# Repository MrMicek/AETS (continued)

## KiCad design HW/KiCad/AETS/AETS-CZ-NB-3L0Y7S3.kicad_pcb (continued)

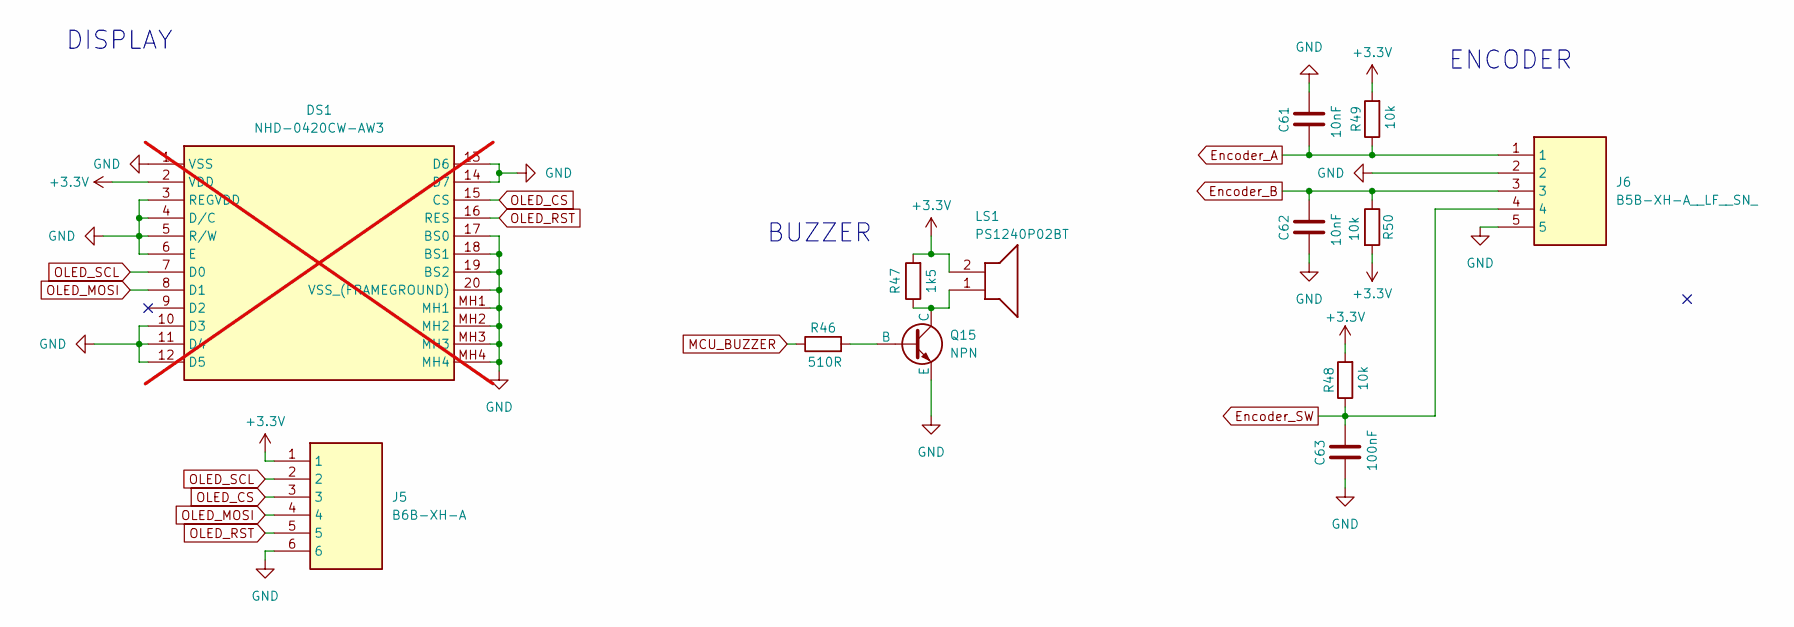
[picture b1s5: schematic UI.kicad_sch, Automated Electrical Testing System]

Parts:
C61, C62: 10nF; C_0805_2012Metric
C63: 100nF; C_0805_2012Metric
DS1: NHD-0420CW-AW3; NHD0420CWAW3; Manufacturer_Part_Number NHD-0420CW-AW3; not fitted
J5: B6B-XH-A; B6BXHA; Manufacturer_Part_Number B6B-XH-A
J6: B5B-XH-A__LF__SN_; SHDR5W64P0X250_1X5_1490X575X700P; Manufacturer_Part_Number B5B-XH-A (LF)(SN)
LS1: PS1240P02BT; Mouser Part Number 810-PS1240P02BT
Q15: NPN; SOT95P240X120-3N
R46: 510R; R_0805_2012Metric
R47: 1k5; R_0603_1608Metric
R48, R49, R50: 10k; R_0805_2012Metric

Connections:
+3.3V: DS1.2 (VDD), J5.1, LS1.2, R47.2, R48.2, R49.2, R50.2; also elsewhere on the board
Encoder_A: C61.2, J6.1, R49.1; also elsewhere on the board
Encoder_B: C62.1, J6.3, R50.1; also elsewhere on the board
Encoder_SW: C63.1, J6.4, R48.1; also elsewhere on the board
GND: C61.1, C62.2, C63.2, DS1.1 (VSS), DS1.3 (REGVDD), DS1.4 (D/C), DS1.5 (R/W), DS1.6 (E), DS1.10 (D3), DS1.11 (D4), DS1.12 (D5), DS1.13 (D6), DS1.14 (D7), DS1.17 (BS0), DS1.18 (BS1), DS1.19 (BS2), DS1.20 (VSS_(FRAMEGROUND)), DS1.MH1, DS1.MH2, DS1.MH3, DS1.MH4, J5.6, J6.2, J6.5, Q15.2 (E); also elsewhere on the board
MCU_BUZZER: R46.1; also elsewhere on the board
unnamed: Q15.1 (B), R46.2
unnamed: LS1.1, Q15.3 (C), R47.1
OLED_CS: DS1.15 (CS), J5.3; also elsewhere on the board
OLED_MOSI: DS1.8 (D1), J5.4; also elsewhere on the board
OLED_RST: DS1.16 (RES), J5.5; also elsewhere on the board
OLED_SCL: DS1.7 (D0), J5.2; also elsewhere on the board

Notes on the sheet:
BUZZER
DISPLAY
ENCODER

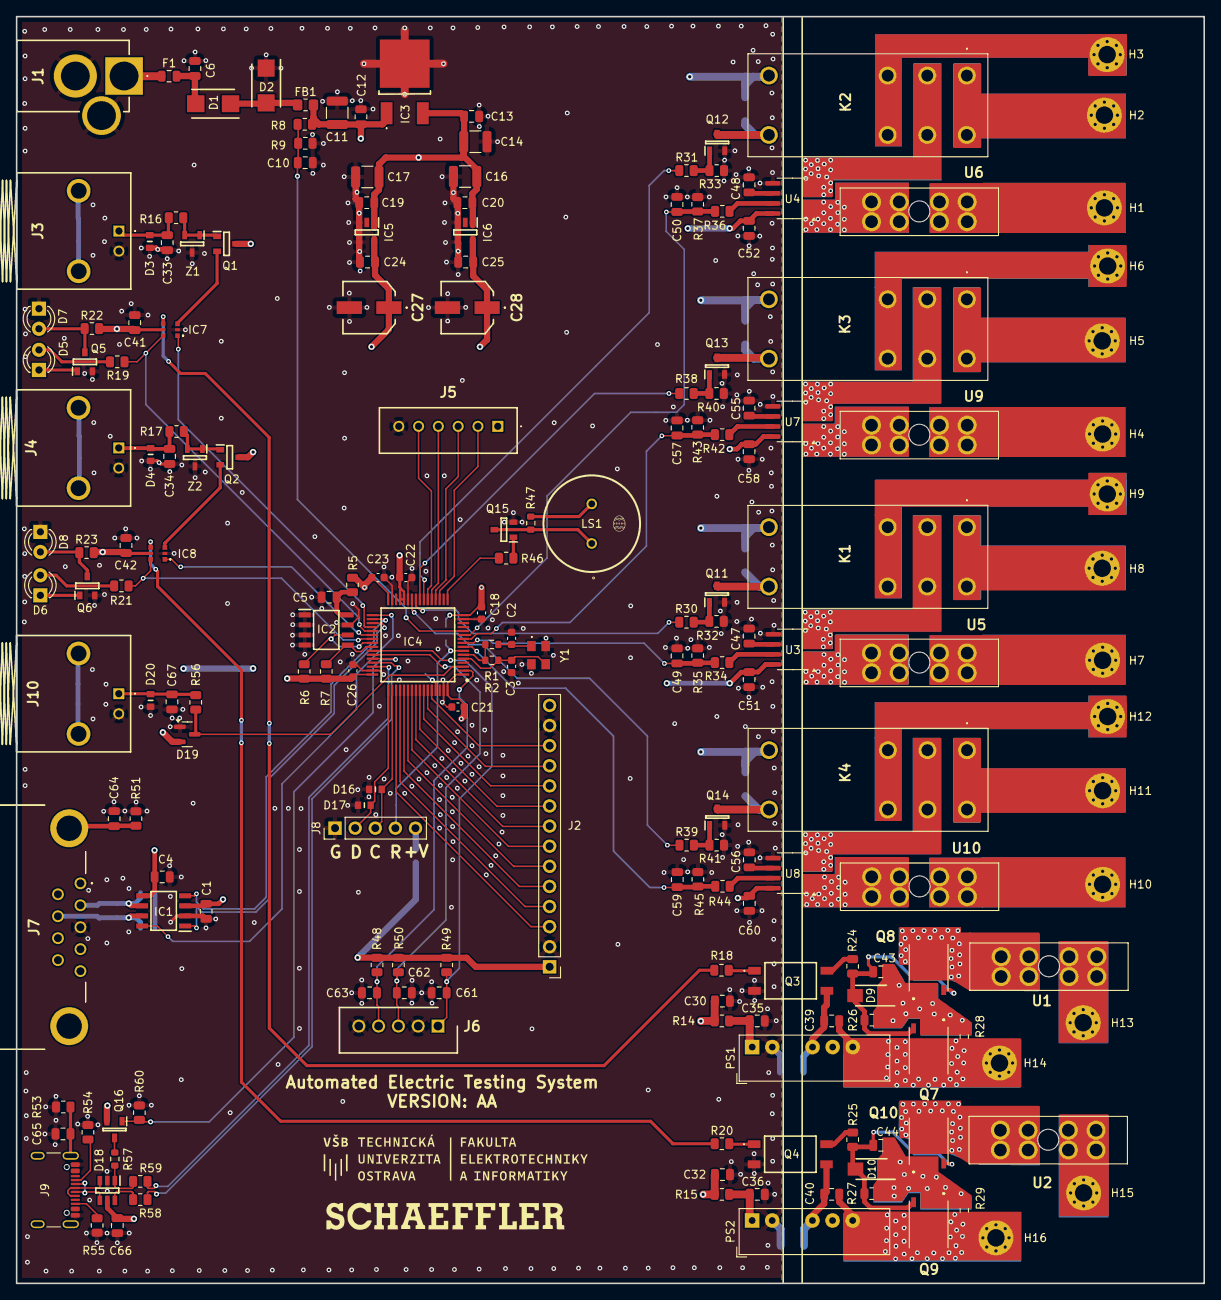
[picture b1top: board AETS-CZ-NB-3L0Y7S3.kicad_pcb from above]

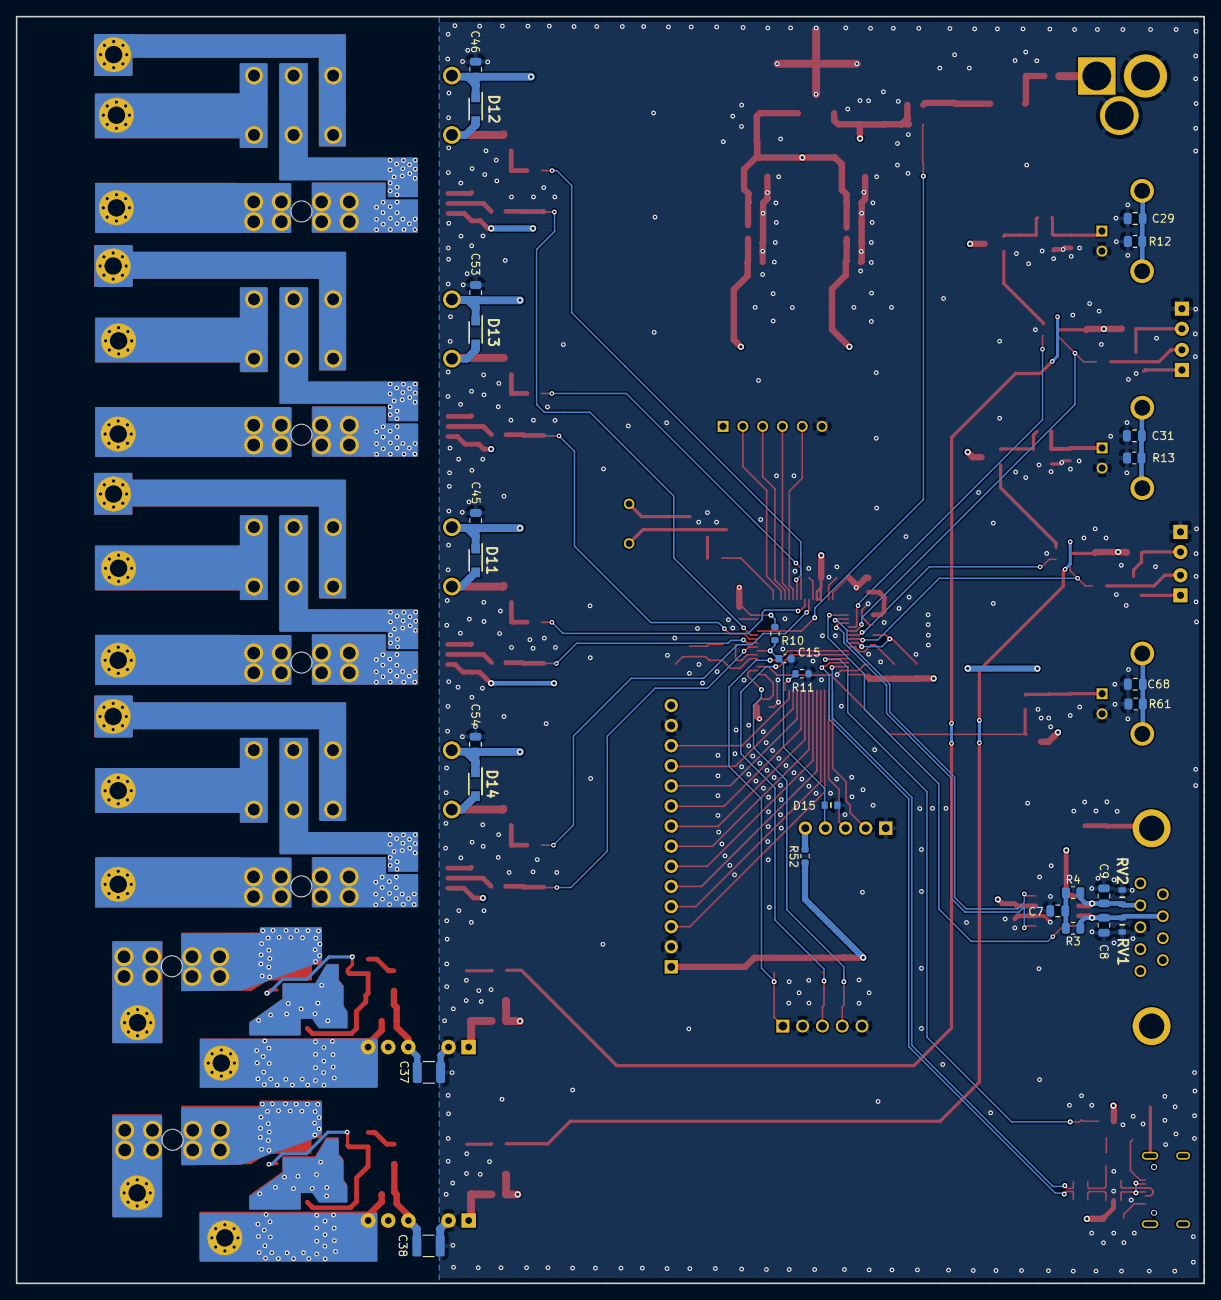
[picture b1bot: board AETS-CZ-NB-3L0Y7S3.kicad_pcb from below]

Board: 4 copper layers, 150.0 x 160.0 mm, 223 parts (28 on the bottom side), 143 nets.

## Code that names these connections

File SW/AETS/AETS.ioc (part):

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Mcu.Name=STM32G474R(B-C-E)Tx
Mcu.Package=LQFP64
Mcu.UserName=STM32G474RETx
PA0.GPIOParameters=GPIO_Label
PA0.GPIO_Label=ADC_VBUS
PA0.Mode=IN1-Single-Ended
PA0.Signal=ADC2_IN1
PA1.GPIOParameters=GPIO_Label
PA1.GPIO_Label=NOTUSED
PA1.Signal=GPIO_Output
PA10.GPIOParameters=GPIO_Label
PA10.GPIO_Label=USB_DIS
PA10.Signal=GPIO_Output
PA11.Mode=Device
PA11.Signal=USB_DM
PA12.Mode=Device
PA12.Signal=USB_DP
PA13.Mode=Serial_Wire
PA13.Signal=SYS_JTMS-SWDIO
PA14.Mode=Serial_Wire
PA14.Signal=SYS_JTCK-SWCLK
PA15.GPIOParameters=GPIO_Label
PA15.GPIO_Label=NOTUSED
PA15.Signal=GPIO_Output
PA2.GPIOParameters=GPIO_Label
PA2.GPIO_Label=NOTUSED
PA2.Signal=GPIO_Output
PA3.GPIOParameters=GPIO_Speed,GPIO_Label
PA3.GPIO_Label=BUZZER
PA3.GPIO_Speed=GPIO_SPEED_FREQ_HIGH
PA3.Signal=S_TIM5_CH4
PA4.GPIOParameters=GPIO_Label
PA4.GPIO_Label=NOTUSED
PA4.Signal=GPIO_Output
PA5.GPIOParameters=GPIO_Label
PA5.GPIO_Label=OLED_SCK
PA5.Mode=Simplex_Bidirectional_Master
PA5.Signal=SPI1_SCK
PA6.GPIOParameters=GPIO_Label
PA6.GPIO_Label=OLED_CS
PA6.Signal=GPIO_Output
PA7.GPIOParameters=GPIO_Label
PA7.GPIO_Label=OLED_MOSI
PA7.Mode=Simplex_Bidirectional_Master
PA7.Signal=SPI1_MOSI
PA8.GPIOParameters=GPIO_Speed,GPIO_Label
PA8.GPIO_Label=ENCODER_A
PA8.GPIO_Speed=GPIO_SPEED_FREQ_MEDIUM
PA8.Signal=S_TIM1_CH1
PA9.GPIOParameters=GPIO_Speed,GPIO_Label
PA9.GPIO_Label=ENCODER_B
PA9.GPIO_Speed=GPIO_SPEED_FREQ_MEDIUM
PA9.Signal=S_TIM1_CH2
PB0.GPIOParameters=GPIO_Label
PB0.GPIO_Label=GPIO_RELAY2
PB0.Signal=GPIO_Output
PB1.GPIOParameters=GPIO_Label
PB1.GPIO_Label=GPIO_RELAY3
PB1.Signal=GPIO_Output
PB10.GPIOParameters=GPIO_Label
PB10.GPIO_Label=NOTUSED
PB10.Signal=GPIO_Output
PB11.GPIOParameters=GPIO_Label
PB11.GPIO_Label=CAN_STB
PB11.Signal=GPIO_Output
PB12.GPIOParameters=GPIO_Speed,GPIO_Label
PB12.GPIO_Label=CAN_RXD
PB12.GPIO_Speed=GPIO_SPEED_FREQ_HIGH
PB12.Mode=FDCAN_Activate
PB12.Signal=FDCAN2_RX
PB13.GPIOParameters=GPIO_Speed,GPIO_Label
PB13.GPIO_Label=CAN_TXD
PB13.GPIO_Speed=GPIO_SPEED_FREQ_HIGH
PB13.Mode=FDCAN_Activate
PB13.Signal=FDCAN2_TX
PB14.GPIOParameters=GPIO_Label
PB14.GPIO_Label=GPIO_MOSFET1
PB14.Signal=GPIO_Output
PB15.GPIOParameters=GPIO_Label
PB15.GPIO_Label=GPIO_MUX1
PB15.Signal=GPIO_Output
PB2.GPIOParameters=GPIO_Label
PB2.GPIO_Label=GPIO_RELAY4
PB2.Signal=GPIO_Output
PB3.GPIOParameters=GPIO_Label
PB3.GPIO_Label=NOTUSED
PB3.Signal=GPIO_Output
PB4.GPIOParameters=GPIO_Label
PB4.GPIO_Label=NOTUSED
PB4.Signal=GPIO_Output
PB5.GPIOParameters=GPIO_Label
PB5.GPIO_Label=NOTUSED
PB5.Signal=GPIO_Output
PB6.GPIOParameters=GPIO_Label
PB6.GPIO_Label=NOTUSED
PB6.Signal=GPIO_Output
PB7.GPIOParameters=GPIO_Label
PB7.GPIO_Label=NOTUSED
PB7.Signal=GPIO_Output
PB9.GPIOParameters=GPIO_Label
PB9.GPIO_Label=NOTUSED
PB9.Signal=GPIO_Output
PC0.GPIOParameters=GPIO_Label,GPIO_Pd
PC0.GPIO_Label=ADC_RELAY4
PC0.GPIO_Pd=GPIO_NOPULL
PC0.Mode=IN6-Single-Ended
PC0.Signal=ADC1_IN6
PC1.GPIOParameters=GPIO_Label,GPIO_Pd
PC1.GPIO_Label=ADC_RELAY3
PC1.GPIO_Pd=GPIO_NOPULL
PC1.Mode=IN7-Single-Ended
PC1.Signal=ADC1_IN7
PC10.GPIOParameters=GPIO_Label
PC10.GPIO_Label=NOTUSED
PC10.Signal=GPIO_Output
PC11.GPIOParameters=GPIO_Label
PC11.GPIO_Label=NOTUSED
PC11.Signal=GPIO_Output
PC12.GPIOParameters=GPIO_Label
PC12.GPIO_Label=NOTUSED
PC12.Signal=GPIO_Output
PC13.GPIOParameters=GPIO_Label,GPIO_ModeDefaultEXTI
PC13.GPIO_Label=ENCODER_SW
PC13.GPIO_ModeDefaultEXTI=GPIO_MODE_IT_FALLING
PC13.Signal=GPXTI13
PC14-OSC32_IN.GPIOParameters=GPIO_Label
PC14-OSC32_IN.GPIO_Label=TRIGGER_OUT
PC14-OSC32_IN.Signal=GPIO_Output
PC15-OSC32_OUT.GPIOParameters=GPIO_Label
PC15-OSC32_OUT.GPIO_Label=NOTUSED
PC15-OSC32_OUT.Signal=GPIO_Output
PC2.GPIOParameters=GPIO_Label
PC2.GPIO_Label=ADC_RELAY2
PC2.Mode=IN8-Single-Ended
PC2.Signal=ADC1_IN8
PC3.GPIOParameters=GPIO_Label
PC3.GPIO_Label=ADC_RELAY1
PC3.Mode=IN9-Single-Ended
PC3.Signal=ADC1_IN9
PC4.GPIOParameters=GPIO_Label
PC4.GPIO_Label=OLED_RST
PC4.Signal=GPIO_Output
PC5.GPIOParameters=GPIO_Label
PC5.GPIO_Label=GPIO_RELAY1
PC5.Signal=GPIO_Output
PC6.GPIOParameters=GPIO_Label
PC6.GPIO_Label=GPIO_MOSFET2
PC6.Signal=GPIO_Output
PC7.GPIOParameters=GPIO_Label
PC7.GPIO_Label=GPIO_MUX2
PC7.Signal=GPIO_Output
PC8.GPIOParameters=GPIO_Speed,GPIO_Label,GPIO_Pu
PC8.GPIO_Label=EEPROM_SCL
PC8.GPIO_Pu=GPIO_NOPULL
PC8.GPIO_Speed=GPIO_SPEED_FREQ_HIGH
PC8.Mode=I2C
PC8.Signal=I2C3_SCL
PC9.GPIOParameters=GPIO_Speed,GPIO_Label,GPIO_Pu
PC9.GPIO_Label=EEPROM_SDA
PC9.GPIO_Pu=GPIO_NOPULL
PC9.GPIO_Speed=GPIO_SPEED_FREQ_HIGH
PC9.Mode=I2C
PC9.Signal=I2C3_SDA
PD2.GPIOParameters=GPIO_Label
PD2.GPIO_Label=NOTUSED
PD2.Signal=GPIO_Output
PF0-OSC_IN.Mode=HSE-External-Oscillator
PF0-OSC_IN.Signal=RCC_OSC_IN
PF1-OSC_OUT.Mode=HSE-External-Oscillator
PF1-OSC_OUT.Signal=RCC_OSC_OUT
RCC.HSE_VALUE=40000000
RCC.SYSCLKFreq_VALUE=144000000
RCC.SYSCLKSource=RCC_SYSCLKSOURCE_PLLCLK
board=custom

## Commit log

2025-02-24 Created HW and SW folders, first schematic draft
2025-12-21 Add application state machine and IO control
2025-12-21 Hook CDC RX into command handler
2025-12-21 Improve CDC command reception
2025-12-21 Fix command parsing after omitted IDs
2025-12-21 Support dual mux channels
2026-01-08 Add command verification checklist
2026-01-08 added changes to usb middleware, some files were missing so i regenerated the code from ioc. Changed one line in current.c, that was i need and absolu value of ma before checking if its under minimal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
2026-01-08 Fix current polarity and relay counter save/load
2026-01-09 Add thousands separator in menu editor
2026-01-09 Changed the cursor look to upArrow acording to internal memory in display code 0xDE
2026-01-09 changed cursor image from > to side arrow represented as 0xDF according to display datasheet ROM A
2026-01-09 Add parameter storage and remote updates
2026-01-15 testing was done according to the text file. some pieces of code needed to be modified.
2026-01-15 moved the PROMPT.txt to main subfolder
2026-01-16 Add testing UI flow and remote gating
2026-01-16 Update test sequencing and screens
2026-01-19 this is the updated code, dont change these implementations
2026-01-19 Clarify test sequencer advance conditions
2026-01-19 Persist relay health set and remaining counts
2026-01-20 Add test current monitoring and profile storage
2026-01-21 Fix test profile gating and current display
2026-01-21 changed visual of r3 when testing
2026-01-23 Changed commands,
2026-01-23 Add CAN and USB telemetry output
2026-01-26 Adjust main loop priorities for test mode
2026-01-27 Run relay and mosfet sequences in parallel
2026-01-27 Run relay/mosfet channels concurrently
2026-01-27 Added last features
2026-01-28 Finnished version - few small tweaks remaining
2026-01-28 updated version of the program. Last thing to do is write CAN output explanation to gethelp cmd
2026-01-29 final version with CAN gh
2026-01-30 added param reset and param list profile commands. added new sounds for saving and loading profiles and added an option to reset parameters in manual mode.
2026-02-04 added confirmation for profile loading and saving
2026-02-05 last update
2026-02-16 relay fix + defining unused pins
2026-02-21 added right amount of switches to relays and better relay trigger selection
2026-03-12 added some features
2026-03-14 fixed overcurrent
2026-03-16 added test
2026-03-17 presentations
2026-03-23 umoznit vypnout current monitoring - default state
    umoznit zapnuti/vypnuti mosfetu a rele pomoci commandu
    navod na rozebrani krabicky
2026-03-23 Souhlas firmy se zveřejněním.pdf
2026-03-24 added pictures
2026-03-25 ADADAS
2026-03-25 get help added
2026-03-26 added manual
2026-03-30 added school presentation
2026-03-31 adad
2026-04-02 added calibration feature to init screen
